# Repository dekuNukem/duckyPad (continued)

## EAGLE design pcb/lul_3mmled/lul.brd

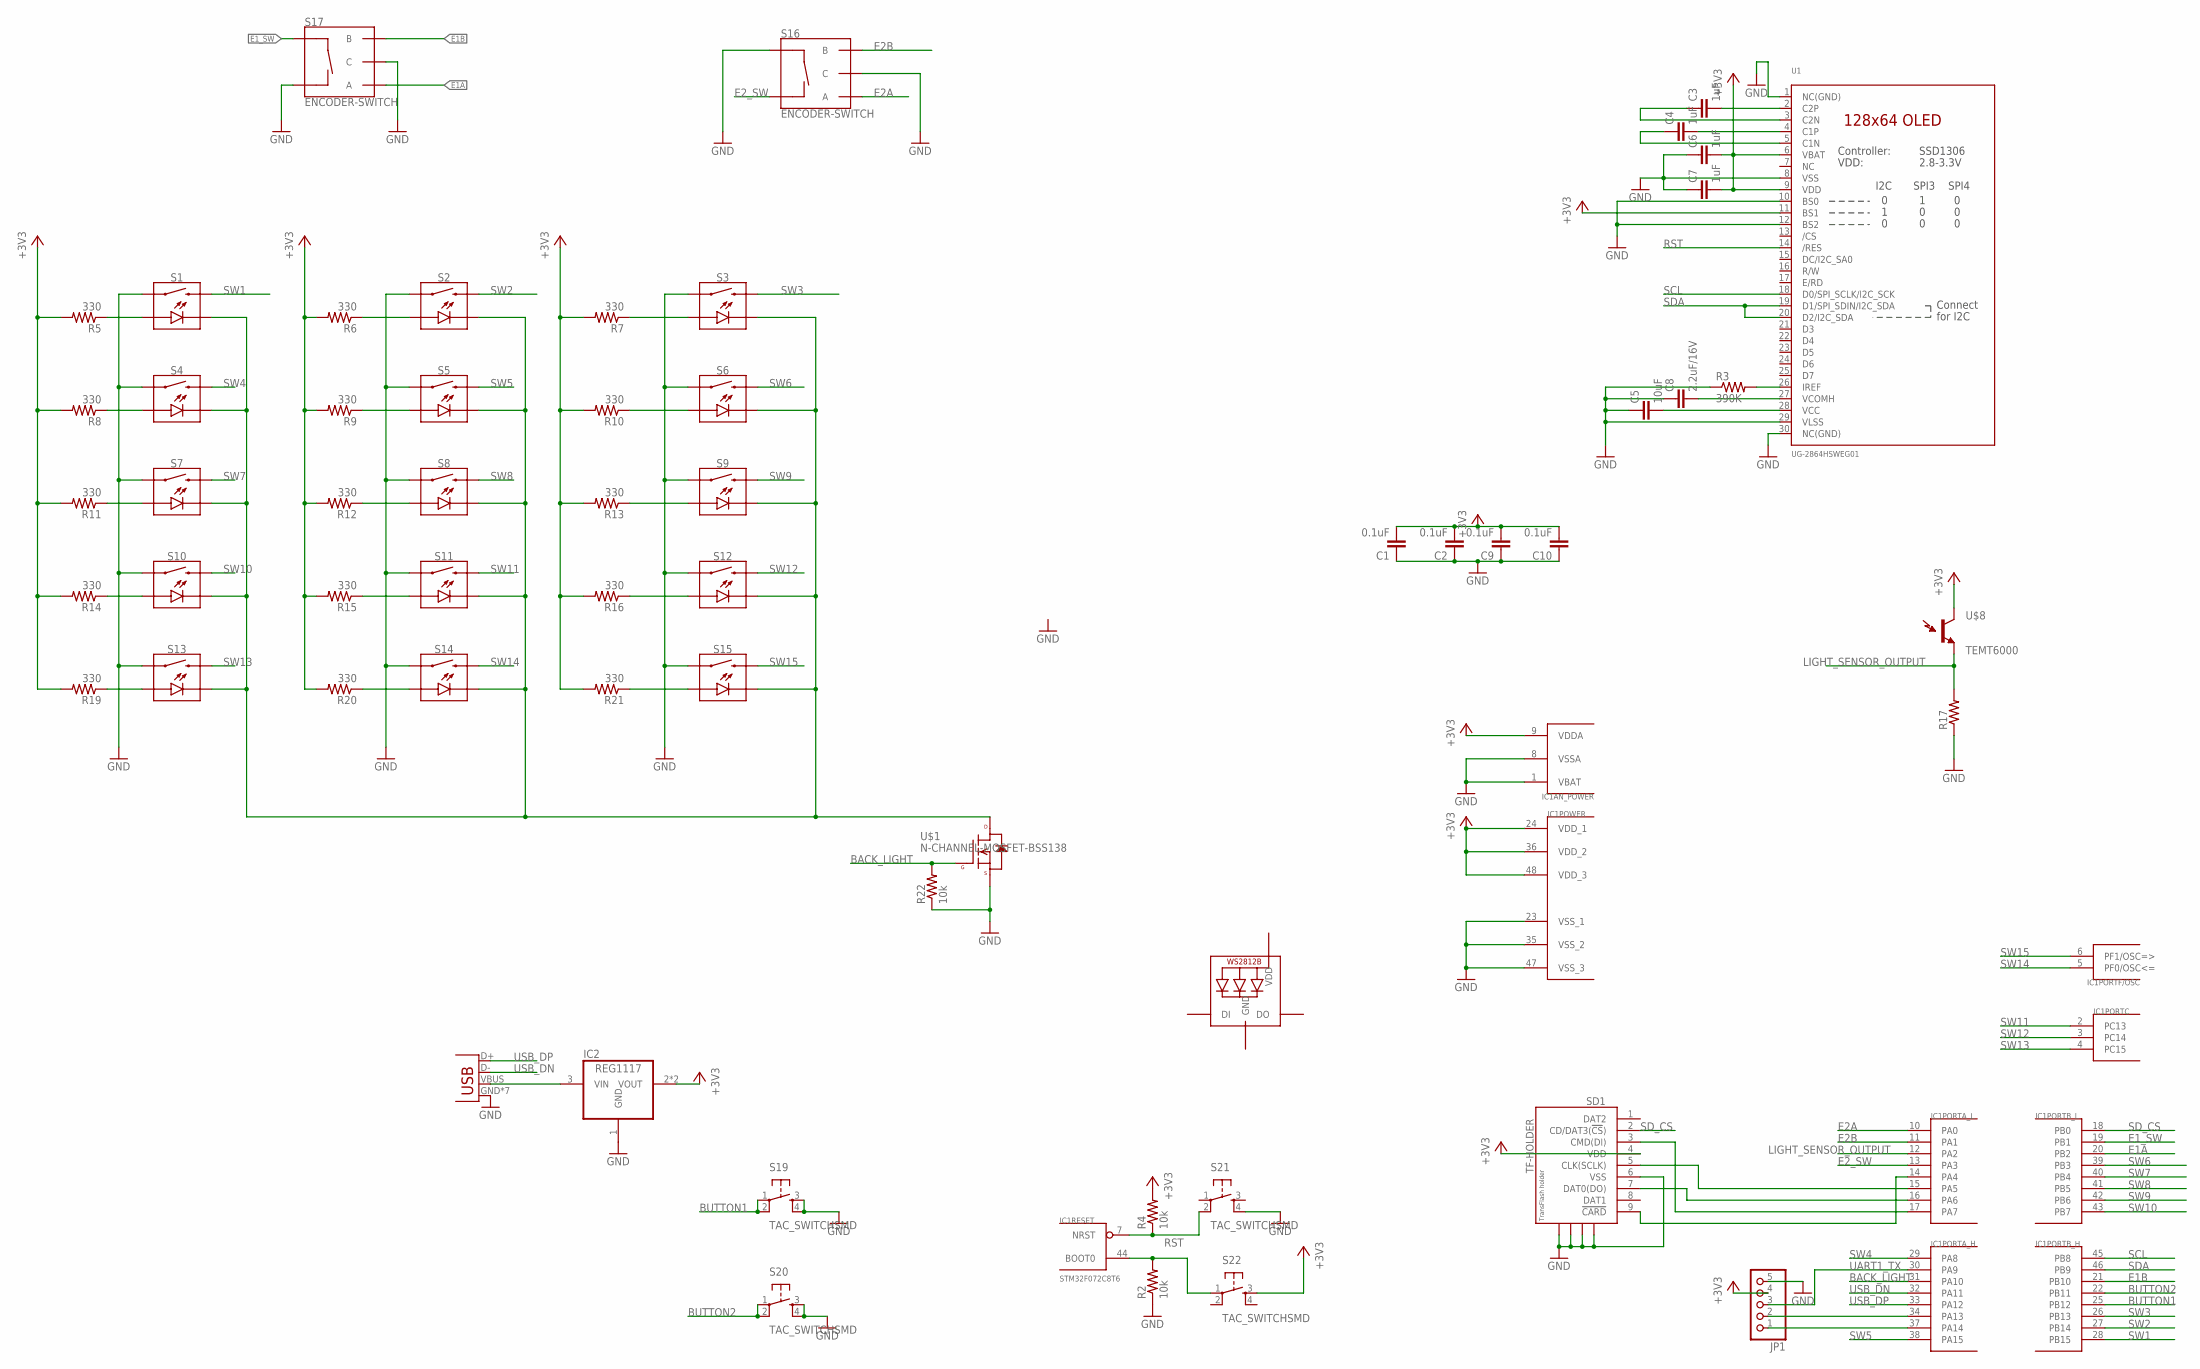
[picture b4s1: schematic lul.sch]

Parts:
C1, C2, C9, C10: 0.1uF; 0805@1
C3, C4, C6, C7: 1uF; 0805@1
C5: 10uF; 0805@1
C8: 2.2uF/16V; 0805@1
IC1: STM32F072C8T6; TQFP48
IC2: REG1117; SOT223
JP1: PINHD-1X5; 1X05
LED1: WS2812B3535; LED3535
R2, R4, R22: 10k; 0805
R3: 390K; 0805
R5, R6, R7, R8, R9, R10, R11, R12, R13, R14, R15, R16, R19, R20, R21: 330; 0805
R17: RESISTOR0805-RES; 0805
S1, S2, S3, S4, S5, S6, S7, S8, S9, S10, S11, S12, S13, S14, S15: MOMENTARY-SWITCH-SPST-LED-PTH-CHERRY; CHERRY-MX-LED
S16, S17: ENCODER-SWITCH; ROTARY_ENC_PLAIN
S19, S20, S21, S22: TAC_SWITCHSMD; TACTILE-SWITCH-SMD
SD1: TF-HOLDER; TF-PULL
U1: UG-2864HSWEG01; UG-2864HSWEG01_0.96IN_WRAPAROUND
U$1: N-CHANNEL-MOSFET-BSS138; SOT23-3
U$8: TEMT6000; TEMT6000-SEN
X1: USB-MICROB

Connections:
+3V3: C1.2, C2.2, C6.2, C7.2, C9.2, C10.2, IC1.9 (VDDA), IC1.24 (VDD_1), IC1.36 (VDD_2), IC1.48 (VDD_3), IC2.2 (VOUT), IC2.4 (VOUT), JP1.4, R4.2, R5.2, R6.2, R7.2, R8.2, R9.2, R10.2, R11.2, R12.2, R13.2, R14.2, R15.2, R16.2, R19.2, R20.2, R21.2, S22.3, SD1.4 (VDD), U1.6 (VBAT), U1.9 (VDD), U1.11 (BS1), U$8.COLLECTOR (C1)
BACK_LIGHT: IC1.31 (PA10), R22.2, U$1.1 (G)
BUTTON1: IC1.25 (PB12), S19.1, S19.2
BUTTON2: IC1.22 (PB11), S20.1, S20.2
E1A: IC1.20 (PB2), S17.A
E1B: IC1.21 (PB10), S17.B
E1_SW: IC1.19 (PB1), S17.SW+
E2A: IC1.10 (PA0), S16.A
E2B: IC1.11 (PA1), S16.B
E2_SW: IC1.13 (PA3), S16.SW-
GND: C1.1, C2.1, C5.1, C6.1, C7.1, C8.1, C9.1, C10.1, IC1.1 (VBAT), IC1.8 (VSSA), IC1.23 (VSS_1), IC1.35 (VSS_2), IC1.47 (VSS_3), IC2.1 (GND), JP1.5, LED1.4 (GND), R2.1, R3.1, R17.1, R22.1, S1.S1 (1), S2.S1 (1), S3.S1 (1), S4.S1 (1), S5.S1 (1), S6.S1 (1), S7.S1 (1), S8.S1 (1), S9.S1 (1), S10.S1 (1), S11.S1 (1), S12.S1 (1), S13.S1 (1), S14.S1 (1), S15.S1 (1), S16.C, S16.SW+, S17.C, S17.SW-, S19.3, S19.4, S20.3, S20.4, S21.4, SD1.6 (VSS), SD1.S1, SD1.S2, SD1.S3, SD1.S4, U1.1 (NC(GND)), U1.8 (VSS), U1.10 (BS0), U1.12 (BS2), U1.29 (VLSS), U1.30 (NC(GND)), U$1.2 (S), X1.GND, X1.P1 (GND), X1.P2 (GND), X1.P3 (GND), X1.P4 (GND), X1.P5 (GND), X1.P6 (GND)
LIGHT_SENSOR_OUTPUT: IC1.12 (PA2), R17.2, U$8.EMITTER (E1)
unnamed: IC2.3 (VIN), X1.VBUS
unnamed: IC1.44 (BOOT0), R2.2, S22.1
unnamed: R3.2, U1.26 (IREF)
unnamed: C3.2, U1.2 (C2P)
unnamed: C3.1, U1.3 (C2N)
unnamed: C4.2, U1.4 (C1P)
unnamed: C4.1, U1.5 (C1N)
unnamed: IC1.15 (PA5), SD1.5 (CLK(SCLK))
unnamed: IC1.16 (PA6), SD1.7 (DAT0(DO))
unnamed: C5.2, U1.28 (VCC)
unnamed: C8.2, U1.27 (VCOMH)
unnamed: IC1.17 (PA7), SD1.3 (CMD(DI))
unnamed: IC1.14 (PA4), SD1.9 (!CARD)
unnamed: R5.1, S1.A
unnamed: R8.1, S4.A
unnamed: R11.1, S7.A
unnamed: R14.1, S10.A
unnamed: R19.1, S13.A
unnamed: R6.1, S2.A
unnamed: R9.1, S5.A
unnamed: R12.1, S8.A
unnamed: R15.1, S11.A
unnamed: R20.1, S14.A
unnamed: R7.1, S3.A
unnamed: R10.1, S6.A
unnamed: R13.1, S9.A
unnamed: R16.1, S12.A
unnamed: R21.1, S15.A
unnamed: S1.K (C), S2.K (C), S3.K (C), S4.K (C), S5.K (C), S6.K (C), S7.K (C), S8.K (C), S9.K (C), S10.K (C), S11.K (C), S12.K (C), S13.K (C), S14.K (C), S15.K (C), U$1.3 (D)
unnamed: IC1.37 (PA14), JP1.1
unnamed: IC1.34 (PA13), JP1.2
RST: IC1.7 (NRST), R4.1, S21.2, U1.14 (/RES)
SCL: IC1.45 (PB8), U1.18 (D0/SPI_SCLK/I2C_SCK)
SDA: IC1.46 (PB9), U1.19 (D1/SPI_SDIN/I2C_SDA), U1.20 (D2/I2C_SDA)
SD_CS: IC1.18 (PB0), SD1.2 (CD/DAT3(!CS!))
SW1: IC1.28 (PB15), S1.S2 (2)
SW2: IC1.27 (PB14), S2.S2 (2)
SW3: IC1.26 (PB13), S3.S2 (2)
SW4: IC1.29 (PA8), S4.S2 (2)
SW5: IC1.38 (PA15), S5.S2 (2)
SW6: IC1.39 (PB3), S6.S2 (2)
SW7: IC1.40 (PB4), S7.S2 (2)
SW8: IC1.41 (PB5), S8.S2 (2)
SW9: IC1.42 (PB6), S9.S2 (2)
SW10: IC1.43 (PB7), S10.S2 (2)
SW11: IC1.2 (PC13), S11.S2 (2)
SW12: IC1.3 (PC14), S12.S2 (2)
SW13: IC1.4 (PC15), S13.S2 (2)
SW14: IC1.5 (PF0/OSC<=), S14.S2 (2)
SW15: IC1.6 (PF1/OSC=>), S15.S2 (2)
UART1_TX: IC1.30 (PA9), JP1.3
USB_DN: IC1.32 (PA11), X1.D-
USB_DP: IC1.33 (PA12), X1.D+
VDD: LED1.2 (VDD)

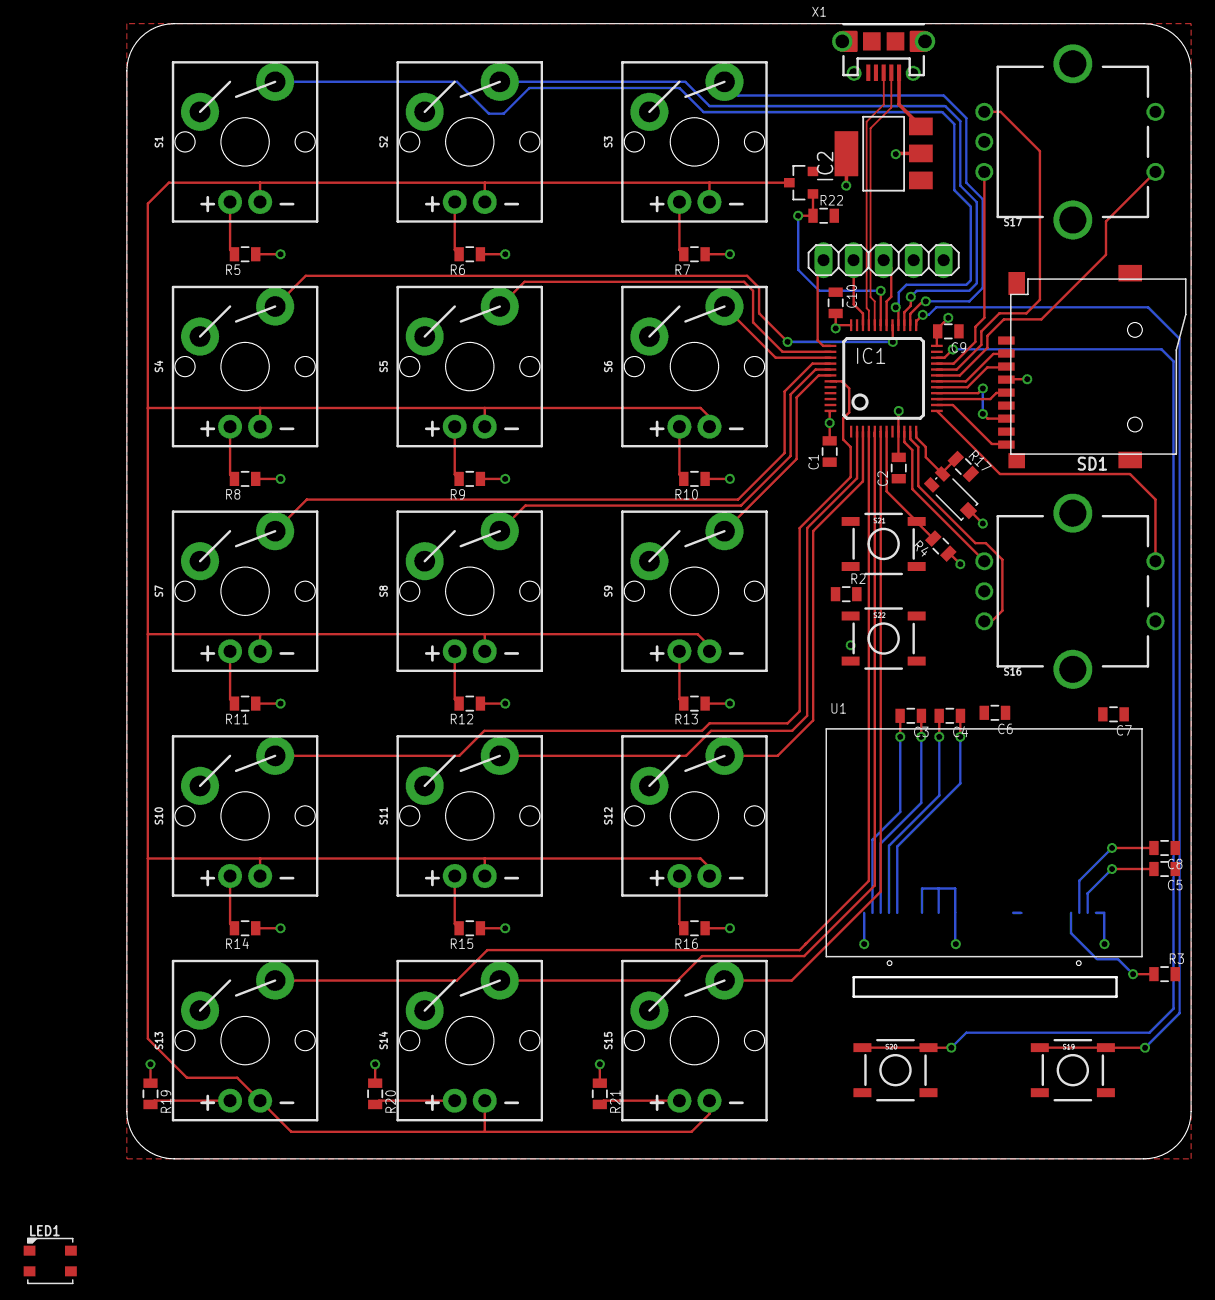
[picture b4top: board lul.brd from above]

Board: 2 copper layers, 90.0 x 96.0 mm, 60 parts (0 on the bottom side), 65 nets.

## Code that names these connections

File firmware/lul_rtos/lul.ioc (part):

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Mcu.Name=STM32F072C(8-B)Tx
Mcu.Package=LQFP48
Mcu.UserName=STM32F072C8Tx
PA0.GPIOParameters=GPIO_PuPd,GPIO_Label,GPIO_ModeDefaultEXTI
PA0.GPIO_Label=E2A
PA0.GPIO_ModeDefaultEXTI=GPIO_MODE_IT_RISING_FALLING
PA0.GPIO_PuPd=GPIO_PULLUP
PA0.Signal=GPXTI0
PA1.GPIOParameters=GPIO_PuPd,GPIO_Label
PA1.GPIO_Label=E2B
PA1.GPIO_PuPd=GPIO_PULLUP
PA1.Signal=GPIO_Input
PA10.GPIOParameters=GPIO_Label
PA10.GPIO_Label=LED_DATA_EN
PA10.Signal=GPIO_Output
PA11.Mode=Device
PA11.Signal=USB_DM
PA12.Mode=Device
PA12.Signal=USB_DP
PA13.Mode=Serial_Wire
PA13.Signal=SYS_SWDIO
PA14.Mode=Serial_Wire
PA14.Signal=SYS_SWCLK
PA15.GPIOParameters=GPIO_PuPd,GPIO_Label
PA15.GPIO_Label=SW5
PA15.GPIO_PuPd=GPIO_PULLUP
PA15.Signal=GPIO_Input
PA2.GPIOParameters=PinState,GPIO_Label
PA2.GPIO_Label=OLED_RESET
PA2.PinState=GPIO_PIN_RESET
PA2.Signal=GPIO_Output
PA3.GPIOParameters=GPIO_PuPd,GPIO_Label
PA3.GPIO_Label=E2_SW
PA3.GPIO_PuPd=GPIO_PULLUP
PA3.Signal=GPIO_Input
PA4.GPIOParameters=GPIO_PuPd,GPIO_Label
PA4.GPIO_Label=CARD_PRESENT
PA4.GPIO_PuPd=GPIO_PULLUP
PA4.Signal=GPIO_Input
PA5.Mode=Full_Duplex_Master
PA5.Signal=SPI1_SCK
PA6.Mode=Full_Duplex_Master
PA6.Signal=SPI1_MISO
PA7.Mode=Full_Duplex_Master
PA7.Signal=SPI1_MOSI
PA8.GPIOParameters=GPIO_PuPd,GPIO_Label
PA8.GPIO_Label=SW4
PA8.GPIO_PuPd=GPIO_PULLUP
PA8.Signal=GPIO_Input
PA9.Mode=Half_duplex(single_wire_mode)
PA9.Signal=USART1_TX
PB0.GPIOParameters=PinState,GPIO_PuPd,GPIO_Label
PB0.GPIO_Label=SD_CS
PB0.GPIO_PuPd=GPIO_NOPULL
PB0.PinState=GPIO_PIN_SET
PB0.Signal=GPIO_Output
PB1.GPIOParameters=GPIO_PuPd,GPIO_Label
PB1.GPIO_Label=E1_SW
PB1.GPIO_PuPd=GPIO_PULLUP
PB1.Signal=GPIO_Input
PB10.GPIOParameters=GPIO_PuPd,GPIO_Label
PB10.GPIO_Label=E1B
PB10.GPIO_PuPd=GPIO_PULLUP
PB10.Signal=GPIO_Input
PB11.GPIOParameters=GPIO_PuPd,GPIO_Label
PB11.GPIO_Label=BUTTON_2
PB11.GPIO_PuPd=GPIO_PULLUP
PB11.Signal=GPIO_Input
PB12.GPIOParameters=GPIO_PuPd,GPIO_Label
PB12.GPIO_Label=BUTTON_1
PB12.GPIO_PuPd=GPIO_PULLUP
PB12.Signal=GPIO_Input
PB13.GPIOParameters=GPIO_PuPd,GPIO_Label
PB13.GPIO_Label=SW1
PB13.GPIO_PuPd=GPIO_PULLUP
PB13.Signal=GPIO_Input
PB14.GPIOParameters=GPIO_PuPd,GPIO_Label
PB14.GPIO_Label=SW2
PB14.GPIO_PuPd=GPIO_PULLUP
PB14.Signal=GPIO_Input
PB15.GPIOParameters=GPIO_PuPd,GPIO_Label
PB15.GPIO_Label=SW3
PB15.GPIO_PuPd=GPIO_PULLUP
PB15.Signal=GPIO_Input
PB2.GPIOParameters=GPIO_PuPd,GPIO_Label,GPIO_ModeDefaultEXTI
PB2.GPIO_Label=E1A
PB2.GPIO_ModeDefaultEXTI=GPIO_MODE_IT_RISING_FALLING
PB2.GPIO_PuPd=GPIO_PULLUP
PB2.Signal=GPXTI2
PB3.GPIOParameters=GPIO_PuPd,GPIO_Label
PB3.GPIO_Label=SW6
PB3.GPIO_PuPd=GPIO_PULLUP
PB3.Signal=GPIO_Input
PB4.GPIOParameters=GPIO_PuPd,GPIO_Label
PB4.GPIO_Label=SW7
PB4.GPIO_PuPd=GPIO_PULLUP
PB4.Signal=GPIO_Input
PB5.GPIOParameters=GPIO_PuPd,GPIO_Label
PB5.GPIO_Label=SW8
PB5.GPIO_PuPd=GPIO_PULLUP
PB5.Signal=GPIO_Input
PB6.GPIOParameters=GPIO_PuPd,GPIO_Label
PB6.GPIO_Label=SW9
PB6.GPIO_PuPd=GPIO_PULLUP
PB6.Signal=GPIO_Input
PB7.GPIOParameters=GPIO_PuPd,GPIO_Label
PB7.GPIO_Label=SW10
PB7.GPIO_PuPd=GPIO_PULLUP
PB7.Signal=GPIO_Input
PB8.Mode=I2C
PB8.Signal=I2C1_SCL
PB9.Mode=I2C
PB9.Signal=I2C1_SDA
PC13.GPIOParameters=GPIO_PuPd,GPIO_Label
PC13.GPIO_Label=SW11
PC13.GPIO_PuPd=GPIO_PULLUP
PC13.Signal=GPIO_Input
PC14-OSC32_IN.GPIOParameters=GPIO_PuPd,GPIO_Label
PC14-OSC32_IN.GPIO_Label=SW12
PC14-OSC32_IN.GPIO_PuPd=GPIO_PULLUP
PC14-OSC32_IN.Signal=GPIO_Input
PC15-OSC32_OUT.GPIOParameters=GPIO_PuPd,GPIO_Label
PC15-OSC32_OUT.GPIO_Label=SW13
PC15-OSC32_OUT.GPIO_PuPd=GPIO_PULLUP
PC15-OSC32_OUT.Signal=GPIO_Input
PF0-OSC_IN.GPIOParameters=GPIO_PuPd,GPIO_Label
PF0-OSC_IN.GPIO_Label=SW14
PF0-OSC_IN.GPIO_PuPd=GPIO_PULLUP
PF0-OSC_IN.Signal=GPIO_Input
PF1-OSC_OUT.GPIOParameters=GPIO_PuPd,GPIO_Label
PF1-OSC_OUT.GPIO_Label=SW15
PF1-OSC_OUT.GPIO_PuPd=GPIO_PULLUP
PF1-OSC_OUT.Signal=GPIO_Input
RCC.SYSCLKFreq_VALUE=40000000
RCC.SYSCLKSource=RCC_SYSCLKSOURCE_PLLCLK
board=lul

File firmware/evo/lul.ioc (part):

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Mcu.Name=STM32F072C(8-B)Tx
Mcu.Package=LQFP48
Mcu.UserName=STM32F072C8Tx
PA0.GPIOParameters=PinState,GPIO_Label
PA0.GPIO_Label=OLED_RESET
PA0.PinState=GPIO_PIN_RESET
PA0.Signal=GPIO_Output
PA1.GPIOParameters=GPIO_PuPd,GPIO_Label
PA1.GPIO_Label=MINUS_BUTTON
PA1.GPIO_PuPd=GPIO_PULLUP
PA1.Signal=GPIO_Input
PA10.GPIOParameters=GPIO_Label
PA10.GPIO_Label=LED_DATA_EN
PA10.Signal=GPIO_Output
PA11.Mode=Device
PA11.Signal=USB_DM
PA12.Mode=Device
PA12.Signal=USB_DP
PA13.Mode=Serial_Wire
PA13.Signal=SYS_SWDIO
PA14.Mode=Serial_Wire
PA14.Signal=SYS_SWCLK
PA15.GPIOParameters=GPIO_PuPd,GPIO_Label
PA15.GPIO_Label=SW5
PA15.GPIO_PuPd=GPIO_PULLUP
PA15.Signal=GPIO_Input
PA2.GPIOParameters=GPIO_PuPd,GPIO_Label
PA2.GPIO_Label=PLUS_BUTTON
PA2.GPIO_PuPd=GPIO_PULLUP
PA2.Signal=GPIO_Input
PA4.GPIOParameters=GPIO_PuPd,GPIO_Label,GPIO_ModeDefaultEXTI
PA4.GPIO_Label=CARD_DETECT
PA4.GPIO_ModeDefaultEXTI=GPIO_MODE_IT_RISING_FALLING
PA4.GPIO_PuPd=GPIO_PULLUP
PA4.Signal=GPXTI4
PA5.Mode=Full_Duplex_Master
PA5.Signal=SPI1_SCK
PA6.Mode=Full_Duplex_Master
PA6.Signal=SPI1_MISO
PA7.Mode=Full_Duplex_Master
PA7.Signal=SPI1_MOSI
PA8.GPIOParameters=GPIO_PuPd,GPIO_Label
PA8.GPIO_Label=SW4
PA8.GPIO_PuPd=GPIO_PULLUP
PA8.Signal=GPIO_Input
PA9.Mode=Half_duplex(single_wire_mode)
PA9.Signal=USART1_TX
PB0.GPIOParameters=PinState,GPIO_PuPd,GPIO_Label
PB0.GPIO_Label=SD_CS
PB0.GPIO_PuPd=GPIO_NOPULL
PB0.PinState=GPIO_PIN_SET
PB0.Signal=GPIO_Output
PB13.GPIOParameters=GPIO_PuPd,GPIO_Label
PB13.GPIO_Label=SW1
PB13.GPIO_PuPd=GPIO_PULLUP
PB13.Signal=GPIO_Input
PB14.GPIOParameters=GPIO_PuPd,GPIO_Label
PB14.GPIO_Label=SW2
PB14.GPIO_PuPd=GPIO_PULLUP
PB14.Signal=GPIO_Input
PB15.GPIOParameters=GPIO_PuPd,GPIO_Label
PB15.GPIO_Label=SW3
PB15.GPIO_PuPd=GPIO_PULLUP
PB15.Signal=GPIO_Input
PB3.GPIOParameters=GPIO_PuPd,GPIO_Label
PB3.GPIO_Label=SW6
PB3.GPIO_PuPd=GPIO_PULLUP
PB3.Signal=GPIO_Input
PB4.GPIOParameters=GPIO_PuPd,GPIO_Label
PB4.GPIO_Label=SW7
PB4.GPIO_PuPd=GPIO_PULLUP
PB4.Signal=GPIO_Input
PB5.GPIOParameters=GPIO_PuPd,GPIO_Label
PB5.GPIO_Label=SW8
PB5.GPIO_PuPd=GPIO_PULLUP
PB5.Signal=GPIO_Input
PB6.GPIOParameters=GPIO_PuPd,GPIO_Label
PB6.GPIO_Label=SW9
PB6.GPIO_PuPd=GPIO_PULLUP
PB6.Signal=GPIO_Input
PB7.GPIOParameters=GPIO_PuPd,GPIO_Label
PB7.GPIO_Label=SW10
PB7.GPIO_PuPd=GPIO_PULLUP
PB7.Signal=GPIO_Input
PB8.GPIOParameters=GPIO_Pu
PB8.GPIO_Pu=GPIO_PULLUP
PB8.Mode=I2C
PB8.Signal=I2C1_SCL
PB9.GPIOParameters=GPIO_Pu
PB9.GPIO_Pu=GPIO_PULLUP
PB9.Mode=I2C
PB9.Signal=I2C1_SDA
PC13.GPIOParameters=GPIO_PuPd,GPIO_Label
PC13.GPIO_Label=SW11
PC13.GPIO_PuPd=GPIO_PULLUP
PC13.Signal=GPIO_Input
PC14-OSC32_IN.GPIOParameters=GPIO_PuPd,GPIO_Label
PC14-OSC32_IN.GPIO_Label=SW12
PC14-OSC32_IN.GPIO_PuPd=GPIO_PULLUP
PC14-OSC32_IN.Signal=GPIO_Input
PC15-OSC32_OUT.GPIOParameters=GPIO_PuPd,GPIO_Label
PC15-OSC32_OUT.GPIO_Label=SW13
PC15-OSC32_OUT.GPIO_PuPd=GPIO_PULLUP
PC15-OSC32_OUT.Signal=GPIO_Input
PF0-OSC_IN.GPIOParameters=GPIO_PuPd,GPIO_Label
PF0-OSC_IN.GPIO_Label=SW14
PF0-OSC_IN.GPIO_PuPd=GPIO_PULLUP
PF0-OSC_IN.Signal=GPIO_Input
PF1-OSC_OUT.GPIOParameters=GPIO_PuPd,GPIO_Label
PF1-OSC_OUT.GPIO_Label=SW15
PF1-OSC_OUT.GPIO_PuPd=GPIO_PULLUP
PF1-OSC_OUT.Signal=GPIO_Input
RCC.SYSCLKFreq_VALUE=40000000
RCC.SYSCLKSource=RCC_SYSCLKSOURCE_PLLCLK
board=lul

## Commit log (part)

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2023-02-14 working on chunked dsb loading
2023-02-14 removed dsb header
2023-02-14 working on chunked load
2023-02-14 before separate var buf
2023-02-14 added banked loading
2023-02-14 cleaned up opcode values
2023-02-14 changed script max size value
2023-02-15 fixed a bug where screen doesnt update when exiting keymap selection screen
2023-02-16 fixed keymap selection bug, changed loop break command to LBREAK
2023-02-16 updated beta information
2023-02-16 updated guide about LBREAK
2023-02-16 fixed version number
2023-02-16 updating UI
2023-02-16 now automatically selects the first profile after loading
2023-02-16 updated version number
2023-02-16 added minimum firmware version check
2023-02-17 added profile import
2023-02-17 clean up doc
2023-02-17 updated link
2023-02-20 added busy check
2023-02-22 updated commands to get current cursor position
2023-02-23 fixed a minor bug
2023-03-01 fixed a HID detection bug
2023-03-02 better handles expression parsing fail
2023-03-02 updated duckyscript 3 vm doc
2023-03-06 Make compatible with pyhidapi (https://github.com/apmorton/pyhidapi).
2023-03-08 fixed a typo
2023-03-11 updated wording
2023-03-11 updated build script
2023-03-11 added back raw sauce
2023-03-11 fixed dead link
2023-03-29 fixed a RNG bug
2023-03-29 feat(keymap): colemak mod-dh keymap for ANSI 104-key
2023-04-09 fixed a SD card timing bug
2023-04-09 updated duckyscript3 sample scripts
2023-04-14 updated opcode number
2023-05-02 getting ready for duckyscript3 release
2023-05-02 working on firmware check
2023-05-02 added firmware version upper and lower bound check both HID and file-based
2023-05-02 updated firmware number
2023-05-02 new branch to prepare for DS3 release
2023-05-02 rearranged files for duckyscript 3 release
2023-05-02 updating doc for duckyscript 3 release
2023-05-02 prepare for mac build
2023-05-02 updated windows build script
2023-05-03 updating getting started guide
2023-05-03 working on duckyscript 3 doc
2023-05-03 changed push script
2023-05-09 working on pcb plate
2023-05-09 fix: COMMAND keyword for macos
    I looks like the `COMMAND` keyword was missing from the ds3 parser, but `RCOMMAND` was working.
2023-05-12 now ignores macOS junk files
2023-05-25 added script to automate the Linux install
2023-06-01 updated plates
2023-06-04 updated linux icon link in install script
2023-06-29 Fix linux installation command
2023-06-30 Added initial colours or previously selected colours to colour picker.
2023-06-30 fixed EMUK release stuck
2023-06-30 working on EMUK
2023-06-30 fixed EMUK laggy
2023-06-30 updated fw version
2023-06-30 trying to fix bug
2023-06-30 hopefully fixed the EMUK bug
2023-06-30 added beta firmware
2023-06-30 changed hole to 13.9mm
2023-07-01 added _TIME_S read-only variable
2023-07-01 releasing new firmware
2023-07-01 minor cleanup
2023-07-02 Add new keyword GOTO_PROFILE_NAME <name>
2023-07-02 make <name> case insensitive
2023-07-13 Update duckyscript_info.md
    Add GOTO_PROFILE_NAME documentation
2023-07-15 add pdf file
2023-07-27 added pdf schematic, cleaned up files
2023-08-02 fixed a bug when typing EMUK too slowly
2023-09-12 added REM_BLOCK and END_REM for block commenting
2023-09-12 fixed code editor highlighting
2023-09-18 added STRINGLN_BLOCK command
2023-09-18 cleanup
2023-09-18 added STRING_BLOCK and STRING_END
2023-09-18 adjusted INJECT_MOD behaviour
2023-09-20 preparing for release
2023-09-20 added notes about debug window
2023-09-20 STRINGLN block now preserves new lines and white spaces
2023-09-20 added block commands description
2023-10-10 automatically expands MOUSE_MOVE values larger than 127
2023-10-12 checks if duckypad is busy before trying to connect
2023-10-14 updated table of contents
2023-10-14 updated doc
2023-10-19 made switch opening smaller
2023-10-24 fixed url
2023-11-11 increased max profile to 64, not sure if i want to keep it that way
2023-11-11 increased max profile to 64 in configurator
2023-11-27 added italian keymap
2023-11-30 STRING splitting if too long
2024-01-09 updated silkscreen
2024-01-22 not replacing TRUE and FALSE inside STRING statements
2024-01-22 fixing backlight brightness bug
2024-03-31 fixing comment detection bugs
2024-06-22 add instructions and shell.nix file to allow users to install in NixOS using nix-shell
2024-08-20 updated blurbs
2024-08-20 more blurbs
2024-09-08 clarify random is inclusive
2024-10-28 updated alu plates
2024-10-28 finished hw socket vias, spare header on BOOT0
2024-10-28 adding more components
2024-10-29 placing components
2024-10-29 added exist_ok
2024-10-29 trying to use new python version for py2app
2024-10-29 minor changes
2024-10-30 clean up files
2024-10-30 adding components
2024-10-30 v4 draft done
2024-11-04 finishing touches
2024-11-04 starting backport
2024-11-04 setting up rtos
2024-11-04 added fonts
2024-11-04 new gitignre
2024-11-04 porting oled
2024-11-05 trying to see if it works without rtos
2024-11-05 oled working
2024-11-05 added cqueue
2024-11-05 added input task file pair
2024-11-27 updated italian key map
2024-12-02 bug fix fw update
2024-12-05 updated sample profiles
2024-12-05 updated assembly instructions
2024-12-07 widened OLED cutout
2024-12-07 updated bottom plate
2024-12-12 usb msc experiment working but very slow
2024-12-13 back to before usb msc
2024-12-13 working on input scanning
2024-12-13 adjusted signal names
2024-12-13 scan working
2024-12-13 switch event queue working
2024-12-18 fixed dead key behaviour
2025-02-13 neopixel working
2025-02-13 nosd screen
2025-02-13 switch back to pcache
2025-02-13 sd eject reset, working on profile loading
2025-02-13 ui draws, profile check
2025-02-13 profile config line load
2025-02-13 added keypress task
2025-02-13 profile draw working
2025-02-13 working on keypress task
2025-02-13 enabled second UART
2025-02-13 UART rx working
2025-02-13 profile switching works
2025-02-14 animation seems working
2025-02-14 settings UI
2025-02-14 testing out heatshrink
2025-02-14 enter settings menu
2025-02-14 OLED dimming and sleeping working
2025-02-14 usb HID mouse send working
2025-02-14 why no 58
2025-02-15 keyboard LED hid message kind of working
2025-02-15 led buffer now also 64b, increased CUSTOM_HID_EPIN_SIZE to 64
2025-02-15 CUSTOM_HID_OutEvent_FS
2025-02-15 better debug print
2025-02-15 correct USB HID values
2025-02-16 cleanup, HID send not working
2025-02-16 HID send working
2025-02-16 kb print working
2025-02-16 before adding dsvm
2025-02-16 ported dsvm, compiles but untested
2025-02-20 fixed read buffer
2025-02-20 testing out dsb execution
2025-02-20 dsb exe working?
2025-02-20 dsb bank switch working
2025-02-21 [200~load_settings~
2025-02-21 save_settings()
2025-02-21 load save gv working
2025-02-21 get_first_keymap
2025-02-21 spi sd neopixel conflict
2025-02-21 still has flickers
2025-02-21 fixed wrong profile name display
2025-02-21 lowered USB interrupt priority
2025-02-21 porting ui draws
2025-02-21 ported keypress_task works but wonky
2025-02-22 load settings and profiles on startup
2025-02-22 troubleshooting
2025-02-22 LED interfering with SD bank switch
2025-02-22 disable interrupt before CS toggle, seems to throw off systick
2025-02-22 timer 2 millisecond timebase not depend on interrupt
2025-02-22 switched millis() and delay_ms() to timer2
2025-02-23 working on dsb_exists cache
2025-02-23 cached dsb exists check working
2025-02-23 settings menu
2025-02-23 disable irq during neopixel tx
2025-02-23 implementing HID commands
2025-02-23 off by 1 fixed
2025-02-23 speed up goto_profile a bit
2025-02-23 adjusted pc-to-dp buffer index, testing out new dumping protocol
2025-02-23 testing out sd walk
2025-02-23 fixed slow HID speed
2025-02-23 remove unused code
2025-02-23 working on sd walk state machine
2025-02-24 working on state machine
2025-02-24 state machine profile and files working
2025-02-24 state machine file open and size
2025-02-24 state machine file dump kinda working
2025-02-24 state machine file dump eof working
2025-02-28 exclusive hid access mode
2025-03-07 md5 working
2025-03-07 hid command enter file access mode
2025-03-07 long press to exit file access mode
2025-03-08 working on file walk hid packet
2025-03-08 sd file walk with payload working
2025-03-08 sd file walk with md5 working
2025-03-09 working on HID dump python script
2025-03-09 hid dump ack, dir, md5 parsing
2025-03-09 sd walk file content working
2025-03-09 sd walk file dump
2025-03-09 md5 hid save and miss list
2025-03-09 HID file open for readingh
2025-03-09 HID file open for reading
2025-03-09 HID file read dump working
2025-03-09 HID full dump working
2025-03-09 saving settings on a timer
2025-03-09 fixed keyup animation not working
2025-03-11 added spreadsheet, cleanup files
2025-03-18 profile format conversion done
2025-03-18 auto enter file access mode
2025-03-29 HID dir commands
2025-04-04 code cleanup
2025-04-06 more info
2025-04-06 using pages
2025-04-15 updated PCB plate
2025-04-21 added some notes
2025-04-24 new firmware
2025-04-25 updated plate
2025-04-25 overhauling doc
2025-04-26 mention configurator
2025-04-26 updated duckyscript doc
2025-04-26 update doc
2025-05-02 update links
2025-05-09 updated sample profiles for latest firmware
2025-05-23 cleanup doc
2025-05-23 working on caching
2025-05-23 working on cache
2025-05-23 trying to free up some memory
2025-05-24 new fw
2025-05-24 updated user guide
2025-05-24 update main page
2025-05-25 update plate files
2025-05-25 added cam files
2025-06-04 added start fresh guide, updated troubleshooting guide
2025-06-04 updated guide
2025-06-04 adjust wording
2025-06-04 adjust wordingh
2025-06-14 updated screenshots
2025-06-29 fixed global variable not working, expanded to 32GVs
2025-06-29 added write and save gv
2025-07-08 fixed HID buffer clear bug
2025-07-09 working on new save_settings
2025-07-09 back to old save_settings
2025-09-22 working on danish keymap
2025-09-22 updated keymap wording
2025-09-22 fix typo
2025-11-09 fixed firmware update guide link
2026-01-17 enabled RTC, still seems to work
2026-01-17 working on new HID descriptor and message, keyboard type working, still need to double check other events
2026-01-17 1000Hz polling?
2026-01-18 added user defined color structs, added set rtc from unix ts function
2026-01-18 porting dsvm2, compiles but not work
2026-01-18 porting dsvm2, stack init
2026-01-18 shaving memory usage, microlib
2026-01-18 switched to arm compiler 6 free up ram
2026-01-18 freeing up ram
2026-01-18 working on safe banked read
2026-01-18 new stack ops
2026-01-18 stack seems work
2026-01-19 makestr memwrite working
2026-01-19 recursion works, turned off debug print
2026-01-21 new exe error
2026-01-21 test
2026-01-21 better error display
2026-01-21 added sps save
2026-01-21 implemented rand, adjust value clamp, added back caching
2026-01-21 new cache funcs
2026-01-21 added sw bitfield
2026-01-21 before enabling rtcbackup
2026-01-21 rtc backup write read working
2026-01-21 RTC_SetFromUnixTimestamp works
2026-01-22 get local time working
2026-01-22 rtc code cleanup
2026-01-22 utc offset and RTC read works, has drift
2026-01-22 adjusted RTC prescaler
2026-01-22 updated HID command and RTC
2026-01-22 draw rtc icon when rtc is set
2026-01-22 hidtx works
2026-01-26 fixed linux empty HID packet bug
2026-01-26 updated firmware version
2026-01-26 Removed unused USART3 code
2026-01-26 added flappy bird
2026-01-26 increased oled i2c clock
2026-01-26 updated cube file
2026-01-26 new circle drawing algoritm
2026-01-26 oled drawing optimisation
2026-01-26 only draws keyboard LED indicator when USB is connected
2026-01-27 fixed RTC update hang
2026-01-27 only draw rtc icon when not sleeping
2026-01-28 added beta fw
2026-02-09 preparing for public release
2026-02-09 doc cleanup
2026-02-11 updated sample profiles for latest fw
2026-03-01 fixed GOTO_PROFILE not working
2026-03-05 new side-push buttons, new bugfix firmware
2026-03-12 Update getting_started.md for launching Mac apps via Spotlight
    Launching apps is not possible via a single shortcut in macOS, as per Apple's documentation (https://support.apple.com/en-au/guide/mac-help/mchlp2271/mac). Application shortcuts are for specific menu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
2026-03-12 Screenshot of launching via Spotlight
2026-03-12 Updated screenshot to correct one
2026-03-12 Removed Mac App Shortcut instructions
2026-03-15 Increased Anykey-to-Abort check frequency
